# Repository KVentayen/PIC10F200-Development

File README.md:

<!--

TOGGLE PREVIEW IN VISUAL STUDIO CODE:
    Ctrl + Shift + V

This space is designated for Markdown resources:
    - General Markdown Documentation: https://markdown-guide.readthedocs.io/en/latest/index.html

    - Markdown in Visual Studio Code Documentation: https://code.visualstudio.com/docs/languages/markdown

-->

# PIC10F200-Development
This a means to learn more about the PIC10F200 Microcontroller.

# Hardware Development

## Fabrication in the CSUB Fab Lab
The PCB Milling Machine in the CSUB Fab Lab are done using PNG files. The following are specifications for the machine:
- Black Lines or shapes in the file are to be milled at the same depth as other lines or shapes in the file
    - Therefore the milled elements such as traces are to be in different files from elements such as the board outline.
- Elements too small of a size (, size is yet to be determined) will not be recognized and will not be documented in the output document.
- Be sure to make the page size the same for all of the files. For example if the page size is 500px by 500px make sure it is consistent with other files.
- Make sure that the resolution is at least 600dpi for the device when exporting the PNG.
- Make sure that the front and the back files of the board are mirrors of each other. (Remember the transformation is dependent on how the actual board is flipped.)
- All holes are resized to 0.090mm
- Trace Width: 0.5mm

## Project Specific Files
PNG Files for this project have the following specifications:
### Version 1.0
- Page Size: 60 mm x 60 mm
- Distance from Page Origin to Board Origin:
    - X Value: 10mm
    - Y Value: 10mm
### Version 1.1
- Page Size: 50 mm x 50 mm
- Distance from Page Origin to Board Origin:
    - X Value: 3mm
    - Y Value: 3mm
### Version 1.2
- Page Size: 50 mm x 50 mm
- Distance from Page Origin to Board Origin:
    - X Value: 3mm
    - Y Value: 3mm

## Ordering PCB Boards
### JLC PCB
#### PCB Board: Green
Standard PCB/PCBA

General Information
- Filename: JLC_PCB-PIC10F200_PCB-V1.2.zip
- Base Material: FR-4
- Layers: 2
- Dimensions: $45 x 45$ mm
- PCB Quantity: 5
- Product Type: Industrial/Consumer Electronics

PCB Specifications
- Different Design: 1
- Delivery Format: Single PCB
- PCB Thickness: 1.6
- PCB Color: Green
- Silkscreen: White
- Surface Finish: LeadFree HASL

High-Spec Options
- Outer Copper Weight: 1 oz
- Via Covering: Tented
- Confirm Production File: No
- Remove Order Number: No
- Flying Probe Test: Fully Test
- Gold Fingers: No
- Castellated Holes: No

#### PCB Board: Purple
Standard PCB/PCBA

General Information
- Filename: JLC_PCB-PIC10F200_PCB-V1.2.zip
- Base Material: FR-4
- Layers: 2
- Dimensions: $45 x 45$ mm
- PCB Quantity: 5
- Product Type: Industrial/Consumer Electronics

PCB Specifications
- Different Design: 1
- Delivery Format: Single PCB
- PCB Thickness: 1.6
- PCB Color: Purple
- Silkscreen: White
- Surface Finish: LeadFree HASL

High-Spec Options
- Outer Copper Weight: 1 oz
- Via Covering: Tented
- Confirm Production File: No
- Remove Order Number: No
- Flying Probe Test: Fully Test
- Gold Fingers: No
- Castellated Holes: No

#### PCB Board: Blue
Standard PCB/PCBA

General Information
- Filename: JLC_PCB-PIC10F200_PCB-V1.2.zip
- Base Material: FR-4
- Layers: 2
- Dimensions: $45 x 45$ mm
- PCB Quantity: 5
- Product Type: Industrial/Consumer Electronics

PCB Specifications
- Different Design: 1
- Delivery Format: Single PCB
- PCB Thickness: 1.6
- PCB Color: Blue
- Silkscreen: White
- Surface Finish: LeadFree HASL

High-Spec Options
- Outer Copper Weight: 1 oz
- Via Covering: Tented
- Confirm Production File: No
- Remove Order Number: No
- Flying Probe Test: Fully Test
- Gold Fingers: No
- Castellated Holes: No

#### PCB Board: Black
Standard PCB/PCBA

General Information
- Filename: JLC_PCB-PIC10F200_PCB-V1.2.zip
- Base Material: FR-4
- Layers: 2
- Dimensions: $45 x 45$ mm
- PCB Quantity: 5
- Product Type: Industrial/Consumer Electronics

PCB Specifications
- Different Design: 1
- Delivery Format: Single PCB
- PCB Thickness: 1.6
- PCB Color: Black
- Silkscreen: White
- Surface Finish: LeadFree HASL

High-Spec Options
- Outer Copper Weight: 1 oz
- Via Covering: Tented
- Confirm Production File: No
- Remove Order Number: No
- Flying Probe Test: Fully Test
- Gold Fingers: No
- Castellated Holes: No

#### Shipping
Method of Delivery: Parcel International Direct

### OSH Park
#### PCB Board: Purple
Regular

#### PCB Board: Black
After Dark (Black Substrate + Clear Mask)

### PCB Way
#### PCB Board: Black
Order Type: Standard PCB

General Information
- Board Type: Single Pieces
- Different Design in Panel: 1
- *Size (single): $45x45$ mm
- *Quantity: 5 pcs
- Layers: 2 Layers
- Material: FR-4
- FR4-TG: TG 150-160
- Thickness: 1.6 mm
- Min Track/ Spacing: 6/6mil
- Min Hole Size: 0.3mm $\uparrow$
- Solder Mask: Green
- Silkscreen: White
- Edge Connector: No
- Surface Finish: HASL lead free
- Via Process: Tenting Vias
- Finished Copper: 1 oz Cu
- Remove pcb identification number: no

Additional Options: No

#### Shipping: United State Postal Service

# Software Development
Programming for the PIC10F200 Microcontroller will be done using the following:
- **PIC10F200 Microcontroller:** Microcontroller used for development in this project
- **MPLAB X IDE:** Integrated Development Environment for programming the Microcontroller
- **MPLAB X IPE:** Integrated Programming Environment for formatting the Microcontroller Directly
- **PICkit 3:** Interface the microcontroller with the computer through USB for programming.
- **USB Adapter (USB Mini to USB 2.0):** Connects PICkit3 (USB Mini) to a computer (USB 2.0)
- **Male to Male, 6 Pin Jumper Wire:** Connects the PICkit3 to the breadboard to interface with the microcontroller
- **Mini Solderless Breadboard:** Interfaces with the Jumper Wire output of the PICkit3 to the PIC10F200

## Study-CircuitBread
In the folder titled: ``Study-CircuitBread`` there are a series of studies from CircuitBread of which may be based on thier designs.

## Project_Files
This folder is a place to put code to test out using the ``PIC10F200``.

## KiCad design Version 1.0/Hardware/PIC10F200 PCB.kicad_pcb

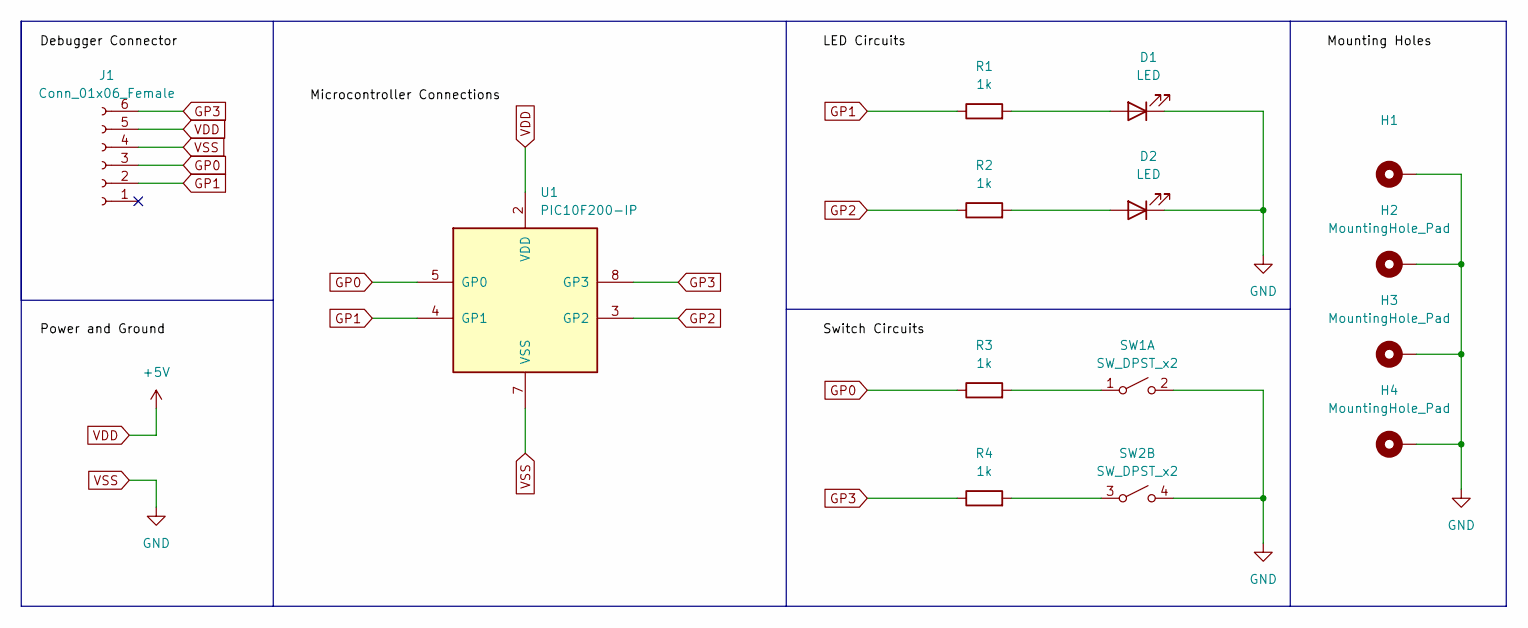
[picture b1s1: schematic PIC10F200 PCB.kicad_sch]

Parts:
D1, D2: LED; LED_D5.0mm
H1: (no value)
H2, H3, H4: MountingHole_Pad
J1: Conn_01x06_Female; PinSocket_1x06_P2.54mm_Horizontal
R1, R2, R3, R4: 1k; R_Axial_DIN0207_L6.3mm_D2.5mm_P10.16mm_Horizontal
SW1, SW2: SW_DPST_x2
U1: PIC10F200-IP; DIP-8_W7.62mm

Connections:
GP0: J1.3, R3.1, U1.5 (GP0)
GP1: J1.2, R1.1, U1.4 (GP1)
GP2: R2.1, U1.3 (GP2)
GP3: J1.6, R4.1, U1.8 (GP3)
unnamed: D1.2 (A), R1.2
unnamed: D2.2 (A), R2.2
unnamed: R3.2, SW1.1 (A)
unnamed: R4.2, SW2.3 (A)
VDD: J1.5, U1.2 (VDD)
VSS: D1.1 (K), D2.1 (K), H1.1, H2.1, H3.1, H4.1, J1.4, SW1.2 (B), SW2.4 (B), U1.7 (VSS)

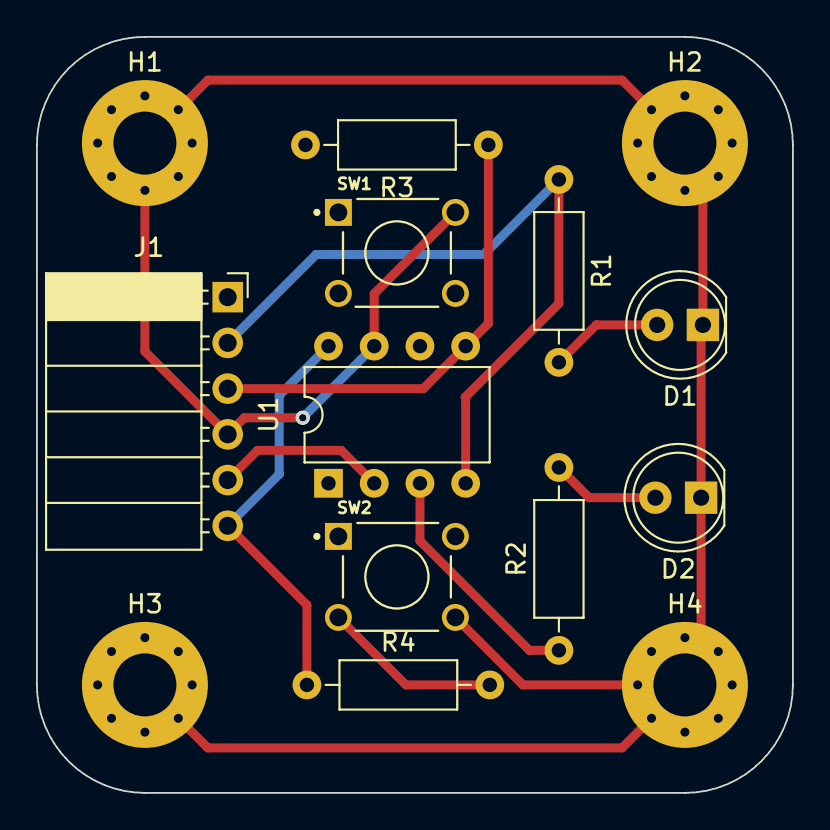
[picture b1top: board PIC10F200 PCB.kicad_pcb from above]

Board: 2 copper layers, 42.0 x 42.0 mm, 14 parts (0 on the bottom side), 10 nets.

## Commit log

2022-06-24 Added first versions of files.
    Added first versions of files.
2022-06-27 Updated README.md and moved modified files to CSUB Fab Lab.
2022-06-29 Updated README.md and SVG File
2022-07-25 Add Version 1.1 and Version 2.1, Update README.md
2022-08-08 README.md is updated to include details about Version 1.2
2022-08-08 Added Version 1.2 Folder and Files
2022-08-11 Moved Hardware Development into Hardware Directory.
2022-08-11 Added Software Development Files to Software Directory.
2022-08-19 Added Software Development details to README.md
2022-10-08 Added raw images of the prototype boards.
2024-02-28 Added and Updated all Files
